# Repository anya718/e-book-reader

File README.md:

Biro Anya-Andreea 332CA

# OpenBook

## Diagrama bloc

## BOM
| Componenta              | Descriere                             | Sursa | Datasheet |
|-------------------------|----------------------------------------|--------|-----------|
| ESP32-C6-WROOM-1-N8     | Multiprotocol Module ESP32             |[Mouser](https://ro.mouser.com/ProductDetail/Espressif-Systems/ESP32-C6-WROOM-1-N8?qs=8Wlm6%252BaMh8ST02Gmwp74cw%3D%3D)|[Datasheet](https://ro.mouser.com/datasheet/2/891/Espressif_ESP32_C6_WROOM_1__Datasheet_V0_1_PRELIMI-3239987.pdf)|
| USB4110-GF-A            | USB Type C Connector                   |[Mouser](https://ro.mouser.com/ProductDetail/GCT/USB4110-GF-A?qs=KUoIvG%2F9IlYiZvIXQjyJeA%3D%3D)|[Datasheet](https://ro.mouser.com/datasheet/2/837/GCT_USB4110_Product_Drawing___20k_cycles-3455479.pdf)|
| 112A-TAAR-R03           | Micro SD Card Socket                   |[Comet](https://store.comet.srl.ro/Catalogue/Product/43497/)|[Datasheet](https://store.comet.bg/download-file.php?id=27596)|
| BME680                  | Air Quality Sensor                     |[Mouser](https://ro.mouser.com/ProductDetail/Bosch-Sensortec/BME680?qs=v271MhAjFHjo0yA%2FC4OnDQ%3D%3D)|[Datasheet](https://ro.mouser.com/datasheet/2/783/BST_BME680_DS001-1509608.pdf)|
| DS3231SN#               | Real Time Clock                        |[Mouser](https://ro.mouser.com/ProductDetail/700-DS3231SN%23)|[Datasheet](https://ro.mouser.com/datasheet/2/609/DS3231-3421123.pdf)|
| EVQ-P4MB3K              | Tactile Switch                         |[Mouser](https://ro.mouser.com/ProductDetail/Panasonic/EVQ-P4MB3K?qs=0aNVN3t2tDvlcmyoDZjvlA%3D%3D)|[Datasheet](https://4donline.ihs.com/images/VipMasterIC/IC/PANA/PANA-S-A0000771493/PANA-S-A0000771493-1.pdf?hkey=CECEF36DEECDED6468708AAF2E19C0C6)|
| MCP73831-2ACI/MC        | Battery Charge Controller              |[Mouser](https://ro.mouser.com/ProductDetail/579-MCP73831-2ACI-MC)|[Datasheet](https://ro.mouser.com/datasheet/2/268/MCP73831_Family_Data_Sheet_DS20001984H-3441711.pdf)|
| MAX17048G+T10           | Battery Management                     |[Mouser](https://ro.mouser.com/ProductDetail/Analog-Devices-Maxim-Integrated/MAX17048G%2bT10?qs=D7PJwyCwLAoGnnn8jEPRBQ%3D%3D)|[Datasheet](https://ro.mouser.com/datasheet/2/609/MAX17048_MAX17049-3469099.pdf)|
| FH34SRJ-24S-0.5SH(99)   | EPD Connector                          |[Mouser](https://ro.mouser.com/ProductDetail/Hirose-Connector/FH34SRJ-24S-0.5SH99?qs=vcbW%252B4%252BSTIpKBl5ap9J8Fw%3D%3D&_gl=1*jvg17l*_ga*dW5kZWZpbmVk*_ga_15W4STQT4T*dW5kZWZpbmVk*_ga_1KQLCYKRX3*dW5kZWZpbmVk)|[Datasheet](https://ro.mouser.com/datasheet/2/185/FH34SRJ_24S_0_5SH_99__CL0580_1255_6_99_2DDrawing_0-1615044.pdf)|
| PRT-14417               | Qwiic JST Connector                    |[Mouser](https://ro.mouser.com/ProductDetail/SparkFun/PRT-14417?qs=wd5RIQLrsJhgdz%2FpmZ%2F3GQ%3D%3D)|[Datasheet](https://ro.mouser.com/datasheet/2/813/Qwiic_Connector_Datasheet-1223982.pdf)|
| W25Q512JVEIQ            | NOR Flash                              |[Mouser](https://ro.mouser.com/ProductDetail/Winbond/W25Q512JVEIQ?qs=l7cgNqFNU1jw6svr3at6tA%3D%3D)|[Datasheet](https://ro.mouser.com/datasheet/2/949/Winbond_W25Q512JV_Datasheet-3240039.pdf)|
| R0402                   | Resistor                               |[Mouser](https://ro.mouser.com/ProductDetail/Panasonic/ERJ-2BWJR051X?qs=pojneS%2F1sjx%252Bdeocf%252BMSog%3D%3D)|[Datasheet](https://industrial.panasonic.com/cdbs/www-data/pdf/RDN0000/AOA0000C313.pdf)|
| B72540T0300K062         | Varistor                               |[Mouser](https://ro.mouser.com/ProductDetail/EPCOS-TDK/B72540T0300K062?qs=dEfas%2FXlABK4d0Dv0OnYYg%3D%3D)|[Datasheet](https://www.tdk-electronics.tdk.com/inf/75/db/CTVS_14/Surge_protection_series.pdf)|
| C0402C475K8PACTU        | Capacitor                              |[Mouser](https://ro.mouser.com/ProductDetail/KEMET/C0402C475K8PACTU?qs=ulEaXIWI0c9ebKRT3r3htg%3D%3D)|[Datasheet](https://ro.mouser.com/datasheet/2/447/KEM_C1006_X5R_SMD-3316465.pdf)|
| T491B107M006AT          | Tantalum Capacitor                     |[Mouser](https://ro.mouser.com/ProductDetail/KEMET/T491B107M006AT?qs=U312oeP%2FpiHOgyk6KO2m0g%3D%3D)|[Datasheet](https://ro.mouser.com/datasheet/2/447/KEM_T2005_T491-3316937.pdf)|
| USBLC6-2SC6Y            | ESD Protection Diode                   |[Mouser](https://ro.mouser.com/ProductDetail/STMicroelectronics/USBLC6-2SC6Y?qs=gNDSiZmRJS%2FOgDexvXkdow%3D%3D)|[Datasheet](https://ro.mouser.com/datasheet/2/389/usblc6_2sc6y-1852505.pdf)|
| PGB1010603MR            | ESD Protection Diode                   |[Mouser](https://ro.mouser.com/ProductDetail/Littelfuse/PGB1010603MR?qs=gu7KAQ731URLg4GSnNNN7Q%3D%3D)|[Datasheet](https://www.littelfuse.com/assetdocs/pulseguard-esd-suppressors-pgb1-datasheet?assetguid=8a337998-d54d-466b-be4e-dc5bcd1f9321)|
| SD0805S020S1R0          | Schottky Diode                         |[Mouser](https://ro.mouser.com/ProductDetail/KYOCERA-AVX/SD0805S020S1R0?qs=jCA%252BPfw4LHbpkAoSnwrdjw%3D%3D)|[Datasheet](https://ro.mouser.com/datasheet/2/40/schottky-3165252.pdf)|
| MBR0530-TP              | Small Signal Schottky Diode            |[Mouser](https://ro.mouser.com/ProductDetail/Micro-Commercial-Components-MCC/MBR0530-TP?qs=KFo7JewZbUECRHkxGanrdg%3D%3D)|[Datasheet](https://ro.mouser.com/datasheet/2/258/MBR0520_MBR0580_SOD123_-2492194.pdf)|
| LSM0603472V             | Single Color LED                       |[Mouser](https://ro.mouser.com/ProductDetail/VCC/LSM0603472V?qs=%252BEew9%252B0nqrBygsW37Z2ISQ%3D%3D)|[Datasheet](https://ro.mouser.com/datasheet/2/423/LSM0603472V_(1)-1379786.pdf)|
| DMG2305UX-7             | MOSFET P-Ch                            |[Mouser](https://ro.mouser.com/ProductDetail/Diodes-Incorporated/DMG2305UX-7?qs=L1DZKBg7t5F%2FNBHrjfxC%252Bg%3D%3D)|[Datasheet](https://www.diodes.com/assets/Datasheets/DMG2305UX.pdf)|
| SI1308EDL-T1-GE3        | MOSFET N-Ch                            |[Mouser](https://ro.mouser.com/ProductDetail/Vishay-Semiconductors/SI1308EDL-T1-GE3?qs=bX1%252BNvsK%2FBramh9tgpOaEw%3D%3D)|[Datasheet](https://www.vishay.com/docs/63399/si1308edl.pdf)|
| CPH3225A                | Supercapacitor                         |[Mouser](https://ro.mouser.com/ProductDetail/Seiko-Semiconductors/CPH3225A?qs=3etwrb1wR%252BhUOph6lAO7eg%3D%3D)|[Datasheet](https://ro.mouser.com/datasheet/2/360/Seiko_Instruments_MicroBattery_E_20230330_2024Jan_-3561061.pdf)|
| 744043680               | SMD Inductor                           |[Mouser](https://ro.mouser.com/ProductDetail/Wurth-Elektronik/744043680?qs=PGXP4M47uW6VkZq%252BkzjrHA%3D%3D)|[Datasheet](https://www.we-online.com/components/products/datasheet/744043680.pdf)|
| BD5229G-TR              | Voltage Detector                       |[Mouser](https://ro.mouser.com/ProductDetail/ROHM-Semiconductor/BD5229G-TR?qs=4kLU8WoGk0vvnhrrYwdszw%3D%3D)|[Datasheet](https://fscdn.rohm.com/en/products/databook/datasheet/ic/power/voltage_detector/bd52xxg-e.pdf)|
| XC6220A331MR-G          | LDO Voltage Regulator                  |[Mouser](https://ro.mouser.com/ProductDetail/Torex-Semiconductor/XC6220A331MR-G?qs=AsjdqWjXhJ8ZSWznL1J0gg%3D%3D)|[Datasheet](https://ro.mouser.com/datasheet/2/760/xc6220-3371556.pdf)|

## Descriere funcționalitate hardware
Proiectul **OpenBook** are ca scop dezvoltarea unui dispozitiv portabil de afișare a informațiilor, cu consum redus de energie, conectivitate Wi-Fi și senzori de mediu.

### Module și interfețe utilizate

- **ESP32-C6** – Microcontroller central cu suport pentru Wi-Fi și BLE. Rulează logica principală și gestionează comunicația cu toate perifericele.
- **BME680** – Senzor pentru calitatea aerului, conectat prin magistrala I2C.
- **DS3231SN** – Ceas de timp real (RTC), conectat I2C.
- **W25Q512JVEIQ** – Memorie NOR Flash SPI pentru stocare de date suplimentară.
- **MAX17048** – Circuit de monitorizare a bateriei, interfață I2C.
- **MCP73831** – Controler de încărcare baterie LiPo.
- **Conector EPD + ecran E-Ink** – Conectat SPI, pentru afișare cu consum redus.
- **Slot microSD** – SPI, pentru citire/scriere fișiere.
- **Buton tactile (EVQ-P4MB3K)** – Intrare digitală, GPIO.
- **Conector USB-C (USB4110-GF-A)** – Încărcare și interfață serială.
- **LED + rezistor + MOSFET** – Indicatoare vizuale, controlate de GPIO.
- **Diodă Schottky, varistori, ESD diode** – Protecție electrică.

### Comunicație și consum

- I2C: folosit pentru BME680, RTC, Battery Gauge
- SPI: utilizat pentru ecranul E-Ink, memoria Flash și SD card
- GPIO: pentru butoane, LED-uri, MOSFET-uri
- UART: pentru debugging via USB
- Estimare consum: 
    - **Mod Activ:** ~220 mA @ 3.3V → ~727 mW  
    - **Mod Sleep:** ~27 µA @ 3.3V → ~0.089 mW  
    - **Autonomie estimată:** ~14 zile cu baterie Li-Po 1200mAh

## Mapare Pini ESP32-C6

| Componentă              | Pin ESP32-C6         | Interfață   |
|-------------------------|----------------------|-------------|
| BME680                  | GPIO4 (SDA), GPIO5 (SCL) | I2C      |
| DS3231SN                | GPIO4, GPIO5         | I2C         |
| E-Ink Display           | GPIO10, GPIO11, ...  | SPI         |
| SD Card                 | GPIO10, GPIO11, ...  | SPI         |
| MAX17048                | GPIO4, GPIO5         | I2C         |
| MCP73831                | GPIO22 (STAT)        | GPIO        |
| Buton                  | GPIO12               | GPIO        |
| LED                    | GPIO13               | GPIO        |
| UART (debug)           | GPIO20 (TX), GPIO21 (RX) | UART    |

## Alte Informații Relevante
- Fișiere schematice și PCB disponibile în `/Hardware`
- Fișiere 3D disponibile în `/Mechanical`
- Randări ale PCB-ului:

- Randări ale dispozitivului:

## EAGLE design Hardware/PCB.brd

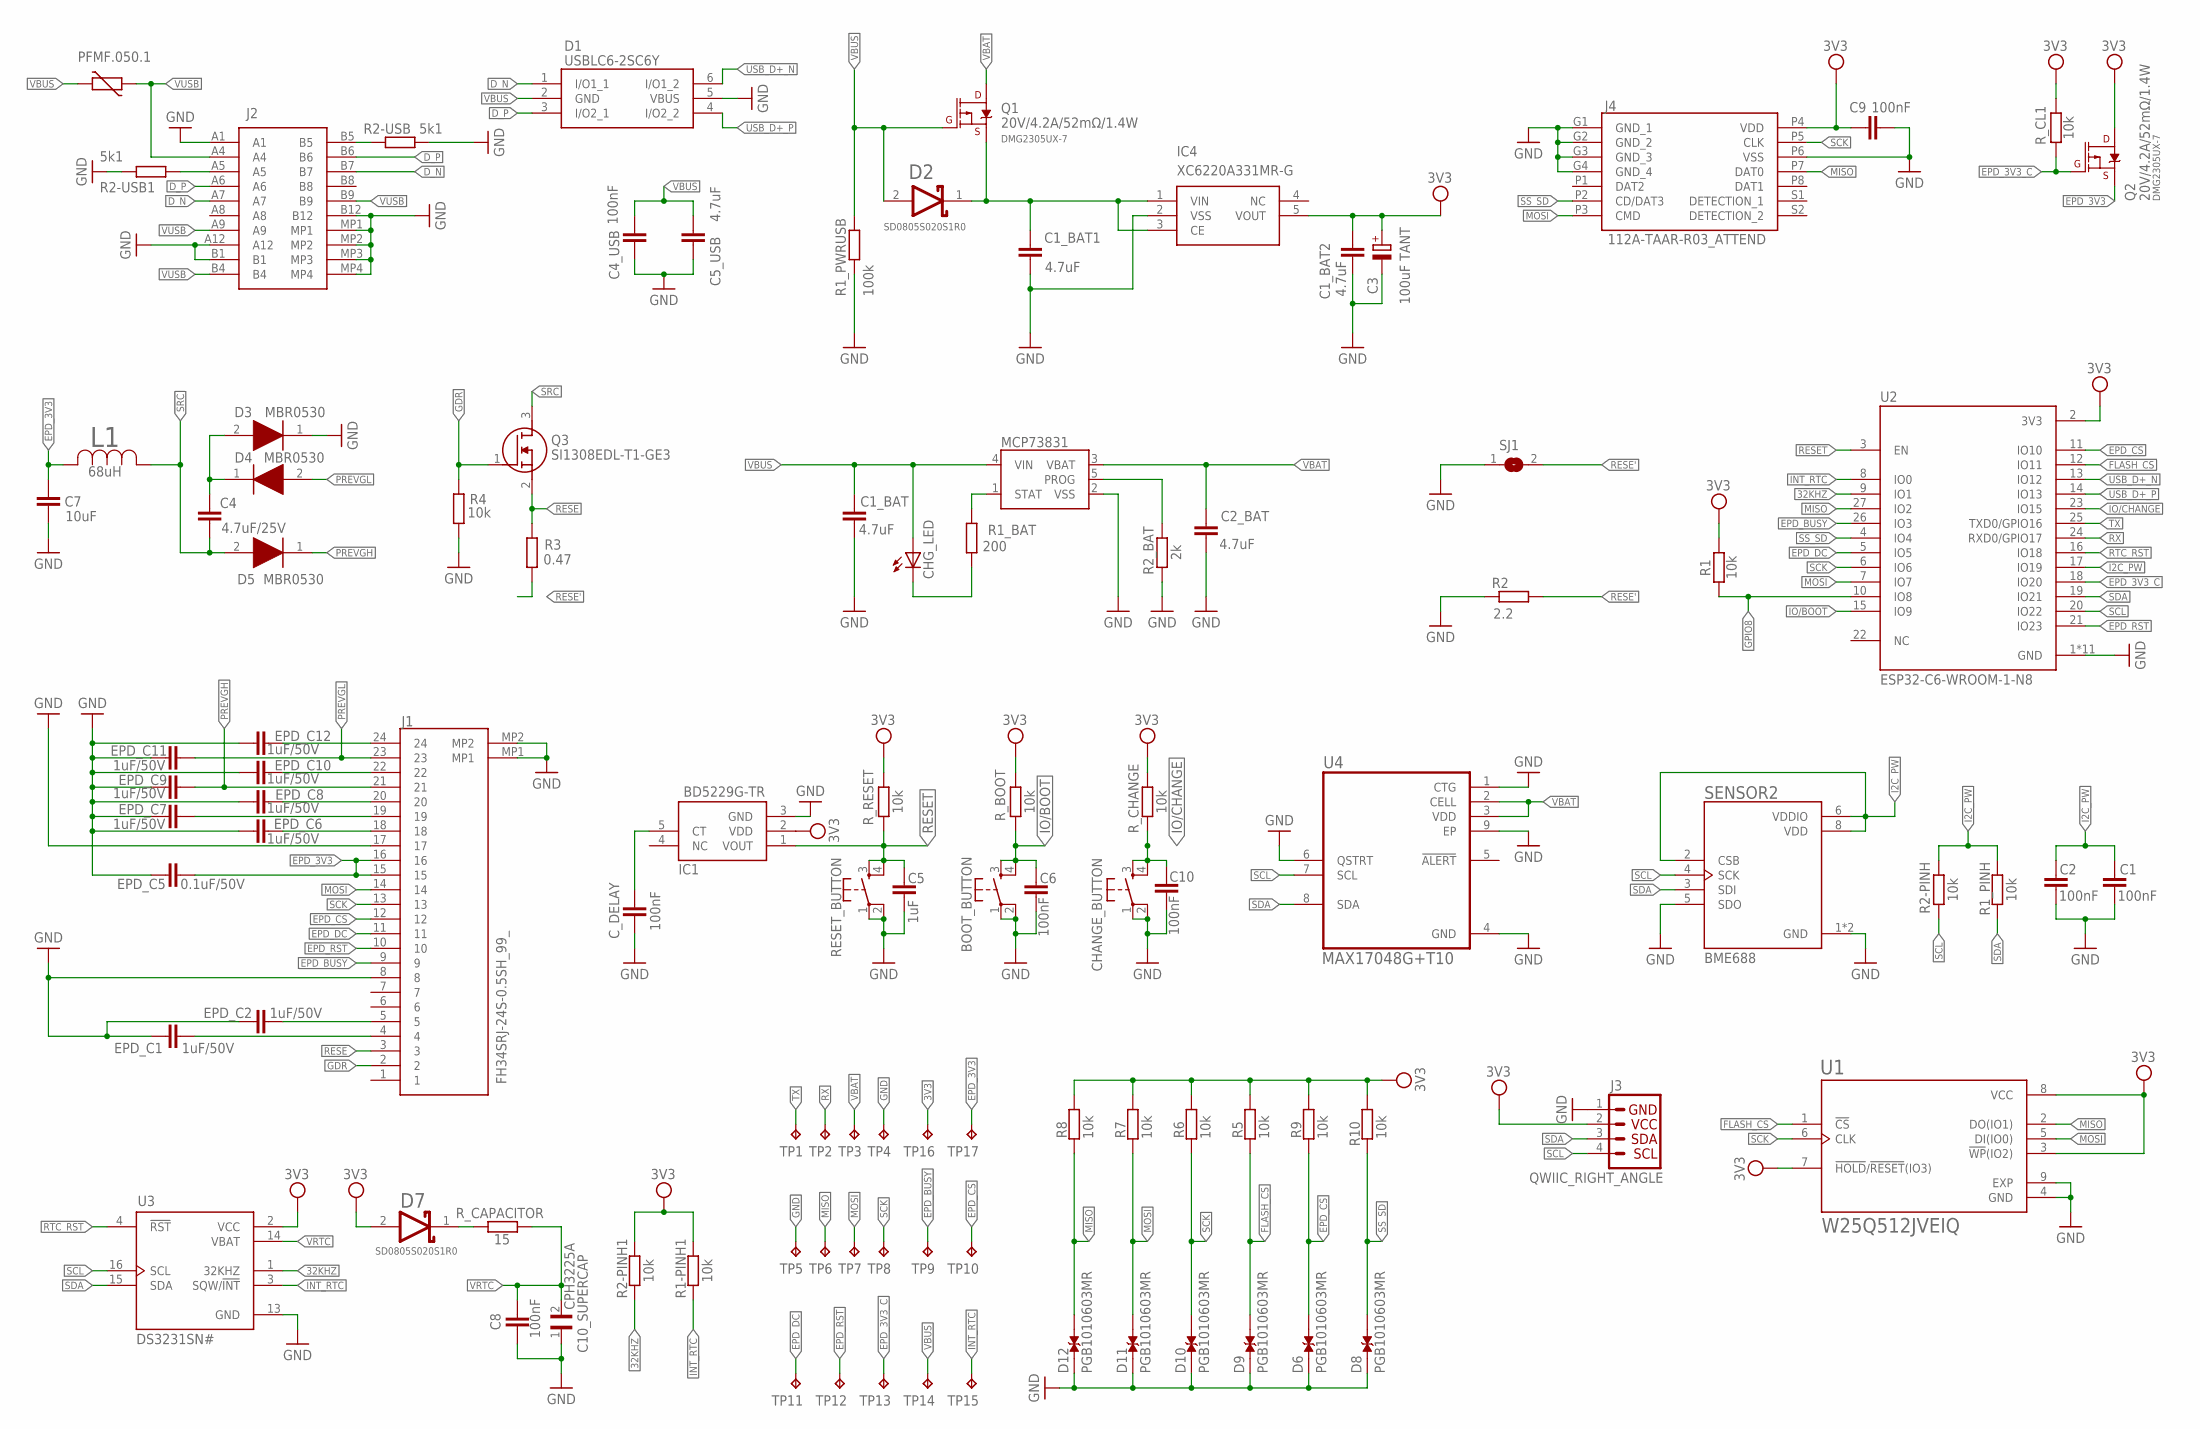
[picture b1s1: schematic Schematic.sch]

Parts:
BOOT_BUTTON: BUTTON_CUSYOMV1; MYBUTTON
C1, C2, C4_USB, C6, C8, C9, C10: 100nF; ESP32_WROVER_EAGLE-LTSPICE_C0402
C1_BAT, C1_BAT1, C1_BAT2, C2_BAT, C5_USB: 4.7uF; ESP32_WROVER_EAGLE-LTSPICE_C0402
C3: 100uF TANT; RCL_CT3528
C4: 4.7uF/25V; ESP32_WROVER_EAGLE-LTSPICE_C0402
C5: 1uF; ESP32_WROVER_EAGLE-LTSPICE_C0402
C7: 10uF; ESP32_WROVER_EAGLE-LTSPICE_C0402
C10_SUPERCAP: CPH3225A; CAPCP3225X100N
CHANGE_BUTTON: BUTTON_CUSYOMV1; MYBUTTON
CHG_LED: ADAFRUIT_LEDCHIP-LED0603; ADAFRUIT_CHIP-LED0603
C_DELAY: 100nF; ESP32_WROVER_EAGLE-LTSPICE_C0402
D1: USBLC6-2SC6Y; SOT95P280X145-6N
D2, D7: ESP32_WROVER_AVX---SD0805S020S1R0_AVX_SD0805S020S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; ESP32_WROVER_AVX---SD0805S020S1R0_AVX_SD0805S020S1R0_0
D3, D4, D5: MBR0530; SOD3716X135N
D6, D8, D9, D10, D11, D12: PGB1010603MR; DIOC1608X36N
EPD_C1, EPD_C2, EPD_C6, EPD_C7, EPD_C8, EPD_C9, EPD_C10, EPD_C11, EPD_C12: 1uF/50V; ESP32_WROVER_EAGLE-LTSPICE_C0402
EPD_C5: 0.1uF/50V; ESP32_WROVER_EAGLE-LTSPICE_C0402
IC1: BD5229G-TR; SOT95P280X125-5N
IC4: XC6220A331MR-G; SOT95P280X120-5N
J1: FH34SRJ-24S-0.5SH_99_; FH34SRJ24S05SH99
J2: SAMACSYS_PARTS_USB4110-GF-A; SAMACSYS_PARTS_USB4110GFA
J3: QWIIC_RIGHT_ANGLE; JST04_1MM_RA
J4: 112A-TAAR-R03_ATTEND; 112ATAARR03ATTEND
L1: 68uH; IND_4828-WE-TPC_WRE
MCP73831: ESP32_WROVER_SPARKFUN-IC-POWER_MCP73831; ESP32_WROVER_SPARKFUN-IC-POWER_SOT23-5
PFMF.050.1: ESP32C6_VARISTORCN1812; ESP32C6_VARISTOR_CT/CN1812
Q1, Q2: 20V/4.2A/52mΩ/1.4W; ESP32_WROVER_SPARKFUN-DISCRETESEMI_SOT23-3
Q3: SI1308EDL-T1-GE3; SOT65P210X110-3N
R1, R1-PINH1, R1_PINH, R2-PINH, R2-PINH1, R4, R5, R6, R7, R8, R9, R10: 10k; ESP32_WROVER_EAGLE-LTSPICE_R0402
R1_BAT: 200; ESP32_WROVER_EAGLE-LTSPICE_R0402
R1_PWRUSB: 100k; ESP32_WROVER_EAGLE-LTSPICE_R0402
R2: 2.2; ESP32_WROVER_EAGLE-LTSPICE_R0402
R2-USB, R2-USB1: 5k1; ESP32_WROVER_EAGLE-LTSPICE_R0402
R2_BAT: 2k; ESP32_WROVER_EAGLE-LTSPICE_R0402
R3: 0.47; ESP32_WROVER_EAGLE-LTSPICE_R0402
RESET_BUTTON: BUTTON_CUSYOMV1; MYBUTTON
R_BOOT: 10k; ESP32_WROVER_EAGLE-LTSPICE_R0402
R_CAPACITOR: 15; ESP32_WROVER_EAGLE-LTSPICE_R0402
R_CHANGE: 10k; ESP32_WROVER_EAGLE-LTSPICE_R0402
R_CL1: 10k; ESP32_WROVER_EAGLE-LTSPICE_R0402
R_RESET: 10k; ESP32_WROVER_EAGLE-LTSPICE_R0402
SENSOR2: ESP32_WROVER_BME680_BME680; ESP32_WROVER_BME680_PSON80P300X300X100-8N
SJ1: SJ
TP1, TP2, TP3, TP4, TP5, TP6, TP7, TP8, TP9, TP10, TP11, TP12, TP13, TP14, TP15, TP16, TP17: TPTP20R; TP20R
U1: W25Q512JVEIQ; SON127P600X800X80-9N
U2: ESP32-C6-WROOM-1-N8; XCVR_ESP32-C6-WROOM-1-N8
U3: DS3231SN#; SOIC127P1032X265-16N
U4: MAX17048G+T10; SON50P200X200X80-9N

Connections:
3V3: C1_BAT2.1, C3.+, C9.1, D7.2 (ANODE), IC1.2 (VDD), IC4.5 (VOUT), J3.2, J4.P4 (VDD), Q2.3 (D), R1.2, R1-PINH1.2, R2-PINH1.2, R5.2, R6.2, R7.2, R8.2, R9.2, R10.2, R_BOOT.2, R_CHANGE.2, R_CL1.2, R_RESET.2, TP16.TP, U1.3 (!WP!(IO2)), U1.7 (!HOLD!/!RESET!(IO3)), U1.8 (VCC), U2.2 (3V3), U3.2 (VCC)
32KHZ: R2-PINH1.1, U2.9 (IO1), U3.1 (32KHZ)
D_N: D1.1 (I/O1_1), J2.A7, J2.B7
D_P: D1.3 (I/O2_1), J2.A6, J2.B6
EPD_3V3: C7.1, EPD_C5.2, J1.15, J1.16, L1.2, Q2.2 (S), TP17.TP
EPD_3V3_C: Q2.1 (G), R_CL1.1, TP13.TP, U2.18 (IO20)
EPD_BUSY: J1.9, TP9.TP, U2.26 (IO3)
EPD_CS: D6.2, J1.12, R9.1, TP10.TP, U2.11 (IO10)
EPD_DC: J1.11, TP11.TP, U2.5 (IO5)
EPD_RST: J1.10, TP12.TP, U2.21 (IO23)
FLASH_CS: D9.2, R5.1, U1.1 (!CS), U2.12 (IO11)
GDR: J1.2, Q3.1 (G), R4.2
GND: BOOT_BUTTON.1, BOOT_BUTTON.2, C1.2, C1_BAT.2, C1_BAT1.2, C1_BAT2.2, C2.2, C2_BAT.2, C3.-, C4_USB.2, C5.2, C5_USB.2, C6.2, C7.2, C8.2, C9.2, C10.2, C10_SUPERCAP.1, CHANGE_BUTTON.1, CHANGE_BUTTON.2, C_DELAY.2, D1.5 (VBUS), D3.1 (K), D6.1, D8.1, D9.1, D10.1, D11.1, D12.1, EPD_C1.1, EPD_C2.1, EPD_C5.1, EPD_C6.1, EPD_C7.1, EPD_C8.1, EPD_C9.1, EPD_C10.1, EPD_C11.1, EPD_C12.1, IC1.3 (GND), IC4.2 (VSS), J1.8, J1.17, J1.MP1, J1.MP2, J2.A1, J2.A12, J2.B1, J2.B12, J2.MP1, J2.MP2, J2.MP3, J2.MP4, J3.1, J4.G1 (GND_1), J4.G2 (GND_2), J4.G3 (GND_3), J4.G4 (GND_4), J4.P6 (VSS), MCP73831.2 (VSS), R1_PWRUSB.1, R2.1, R2-USB.2, R2-USB1.1, R2_BAT.1, R4.1, RESET_BUTTON.1, RESET_BUTTON.2, SENSOR2.1 (GND), SENSOR2.5 (SDO), SENSOR2.7 (GND), SJ1.1, TP4.TP, TP5.TP, U1.4 (GND), U1.9 (EXP), U2.1 (GND), U2.28 (GND), U2.29_1 (GND), U2.29_2 (GND), U2.29_3 (GND), U2.29_4 (GND), U2.29_5 (GND), U2.29_6 (GND), U2.29_7 (GND), U2.29_8 (GND), U2.29_9 (GND), U3.13 (GND), U4.1 (CTG), U4.4 (GND), U4.6 (QSTRT), U4.9 (EP)
GPIO8: R1.1, U2.10 (IO8)
I2C_PW: C1.1, C2.1, R1_PINH.2, R2-PINH.2, SENSOR2.2 (CSB), SENSOR2.6 (VDDIO), SENSOR2.8 (VDD), U2.17 (IO19)
INT_RTC: R1-PINH1.1, TP15.TP, U2.8 (IO0), U3.3 (SQW/!INT)
IO/BOOT: BOOT_BUTTON.3, BOOT_BUTTON.4, C6.1, R_BOOT.1, U2.15 (IO9)
IO/CHANGE: C10.1, CHANGE_BUTTON.3, CHANGE_BUTTON.4, R_CHANGE.1, U2.23 (IO15)
MISO: D12.2, J4.P7 (DAT0), R8.1, TP6.TP, U1.2 (DO(IO1)), U2.27 (IO2)
MOSI: D11.2, J1.14, J4.P3 (CMD), R7.1, TP7.TP, U1.5 (DI(IO0)), U2.7 (IO7)
unnamed: J2.A5, R2-USB1.2
unnamed: C1_BAT1.1, D2.1 (CATHODE), IC4.1 (VIN), IC4.3 (CE), Q1.2 (S)
unnamed: C_DELAY.1, IC1.5 (CT)
unnamed: C4.1, D3.2 (A), D4.1 (K)
unnamed: MCP73831.1 (STAT), R1_BAT.2
unnamed: CHG_LED.C, R1_BAT.1
unnamed: MCP73831.5 (PROG), R2_BAT.2
unnamed: J2.B5, R2-USB.1
unnamed: EPD_C1.2, J1.4
unnamed: EPD_C2.2, J1.5
unnamed: D7.1 (CATHODE), R_CAPACITOR.2
unnamed: EPD_C6.2, J1.18
unnamed: EPD_C7.2, J1.19
unnamed: EPD_C8.2, J1.20
unnamed: EPD_C10.2, J1.22
unnamed: EPD_C12.2, J1.24
PREVGH: D5.1 (K), EPD_C9.2, J1.21
PREVGL: D4.2 (A), EPD_C11.2, J1.23
RESE: J1.3, Q3.2 (S), R3.2
RESE': R2.2, R3.1, SJ1.2
RESET: C5.1, IC1.1 (VOUT), RESET_BUTTON.3, RESET_BUTTON.4, R_RESET.1, U2.3 (EN)
RTC_RST: U2.16 (IO18), U3.4 (!RST)
RX: TP2.TP, U2.24 (RXD0/GPIO17)
SCK: D10.2, J1.13, J4.P5 (CLK), R6.1, TP8.TP, U1.6 (CLK), U2.6 (IO6)
SCL: J3.4, R2-PINH.1, SENSOR2.4 (SCK), U2.20 (IO22), U3.16 (SCL), U4.7 (SCL)
SDA: J3.3, R1_PINH.1, SENSOR2.3 (SDI), U2.19 (IO21), U3.15 (SDA), U4.8 (SDA)
SRC: C4.2, D5.2 (A), L1.1, Q3.3 (D)
SS_SD: D8.2, J4.P2 (CD/DAT3), R10.1, U2.4 (IO4)
TX: TP1.TP, U2.25 (TXD0/GPIO16)
USB_D+_N: D1.6 (I/O1_2), U2.13 (IO12)
USB_D+_P: D1.4 (I/O2_2), U2.14 (IO13)
VBAT: C2_BAT.1, MCP73831.3 (VBAT), Q1.3 (D), TP3.TP, U4.2 (CELL), U4.3 (VDD)
VBUS: C1_BAT.1, C4_USB.1, C5_USB.1, CHG_LED.A, D1.2 (GND), D2.2 (ANODE), MCP73831.4 (VIN), PFMF.050.1.2, Q1.1 (G), R1_PWRUSB.2, TP14.TP
VRTC: C8.1, C10_SUPERCAP.2, R_CAPACITOR.1, U3.14 (VBAT)
VUSB: J2.A4, J2.A9, J2.B4, J2.B9, PFMF.050.1.1

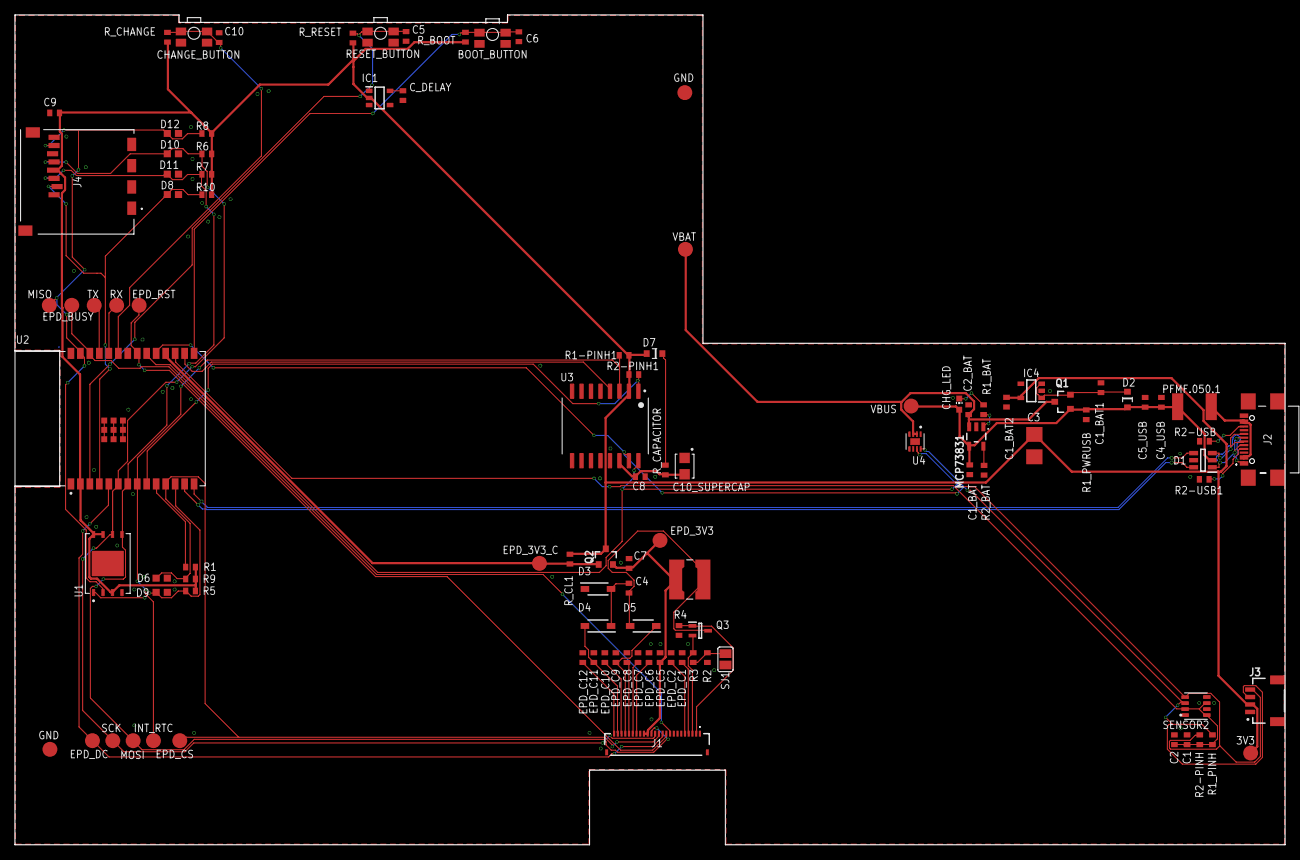
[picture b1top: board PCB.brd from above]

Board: 2 copper layers, 170.2 x 111.2 mm, 103 parts (0 on the bottom side), 55 nets.

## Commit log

2025-04-06 Import project
2025-04-16 Changed images.
2025-04-16 Added README information.
2025-04-16 Updated sch brd and 3d files.
2025-04-16 Added block diagram.
2025-04-16 Updated block diagram and added to README
2025-04-16 Finished README.

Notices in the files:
parts and their libraries:
COPYRIGHT: Copyright (C) 2024 Ultra Librarian. All rights reserved.
